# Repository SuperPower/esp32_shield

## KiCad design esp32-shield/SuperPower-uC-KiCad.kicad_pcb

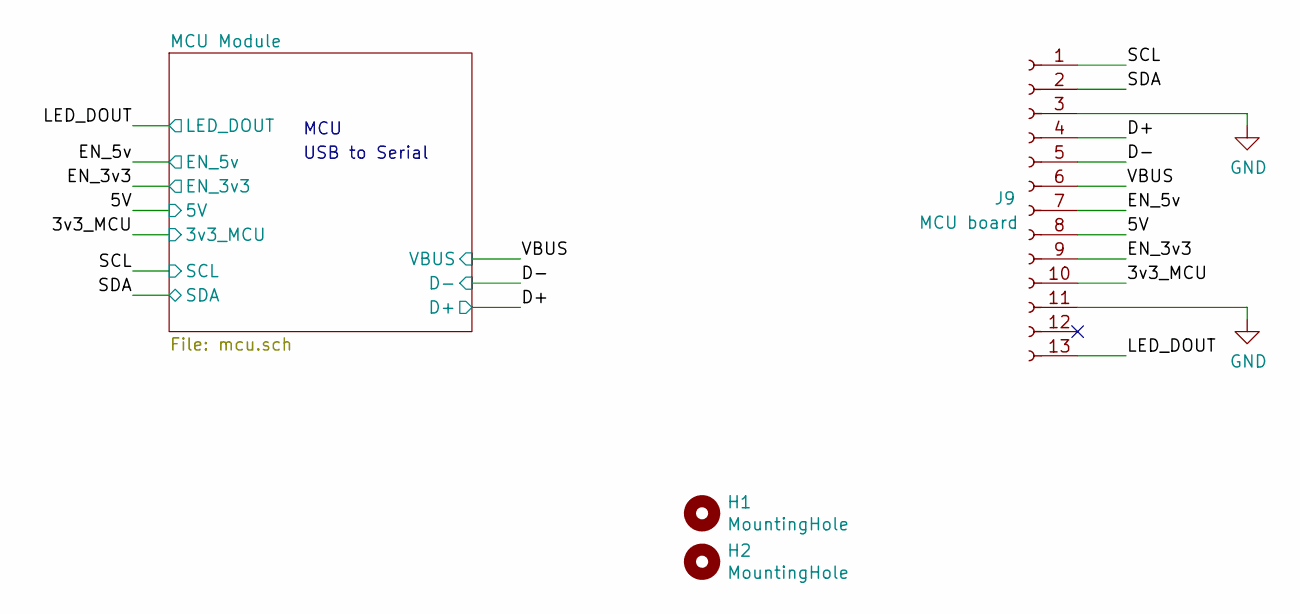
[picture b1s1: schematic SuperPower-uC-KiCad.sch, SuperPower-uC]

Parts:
H1, H2: MountingHole; MountingHole_2.7mm_M2.5_ISO7380
J9: MCU board; PinHeader_1x13_P2.54mm_Vertical

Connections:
/3v3_MCU: J9.10; also elsewhere on the board
/5V: J9.8; also elsewhere on the board
/D+: J9.4; also elsewhere on the board
/D-: J9.5; also elsewhere on the board
/EN_3v3: J9.9; also elsewhere on the board
/EN_5v: J9.7; also elsewhere on the board
/LED_DOUT: J9.13; also elsewhere on the board
/SCL: J9.1; also elsewhere on the board
/SDA: J9.2; also elsewhere on the board
/VBUS: J9.6; also elsewhere on the board
GND: J9.3, J9.11; also elsewhere on the board

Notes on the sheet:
MCU
USB to Serial

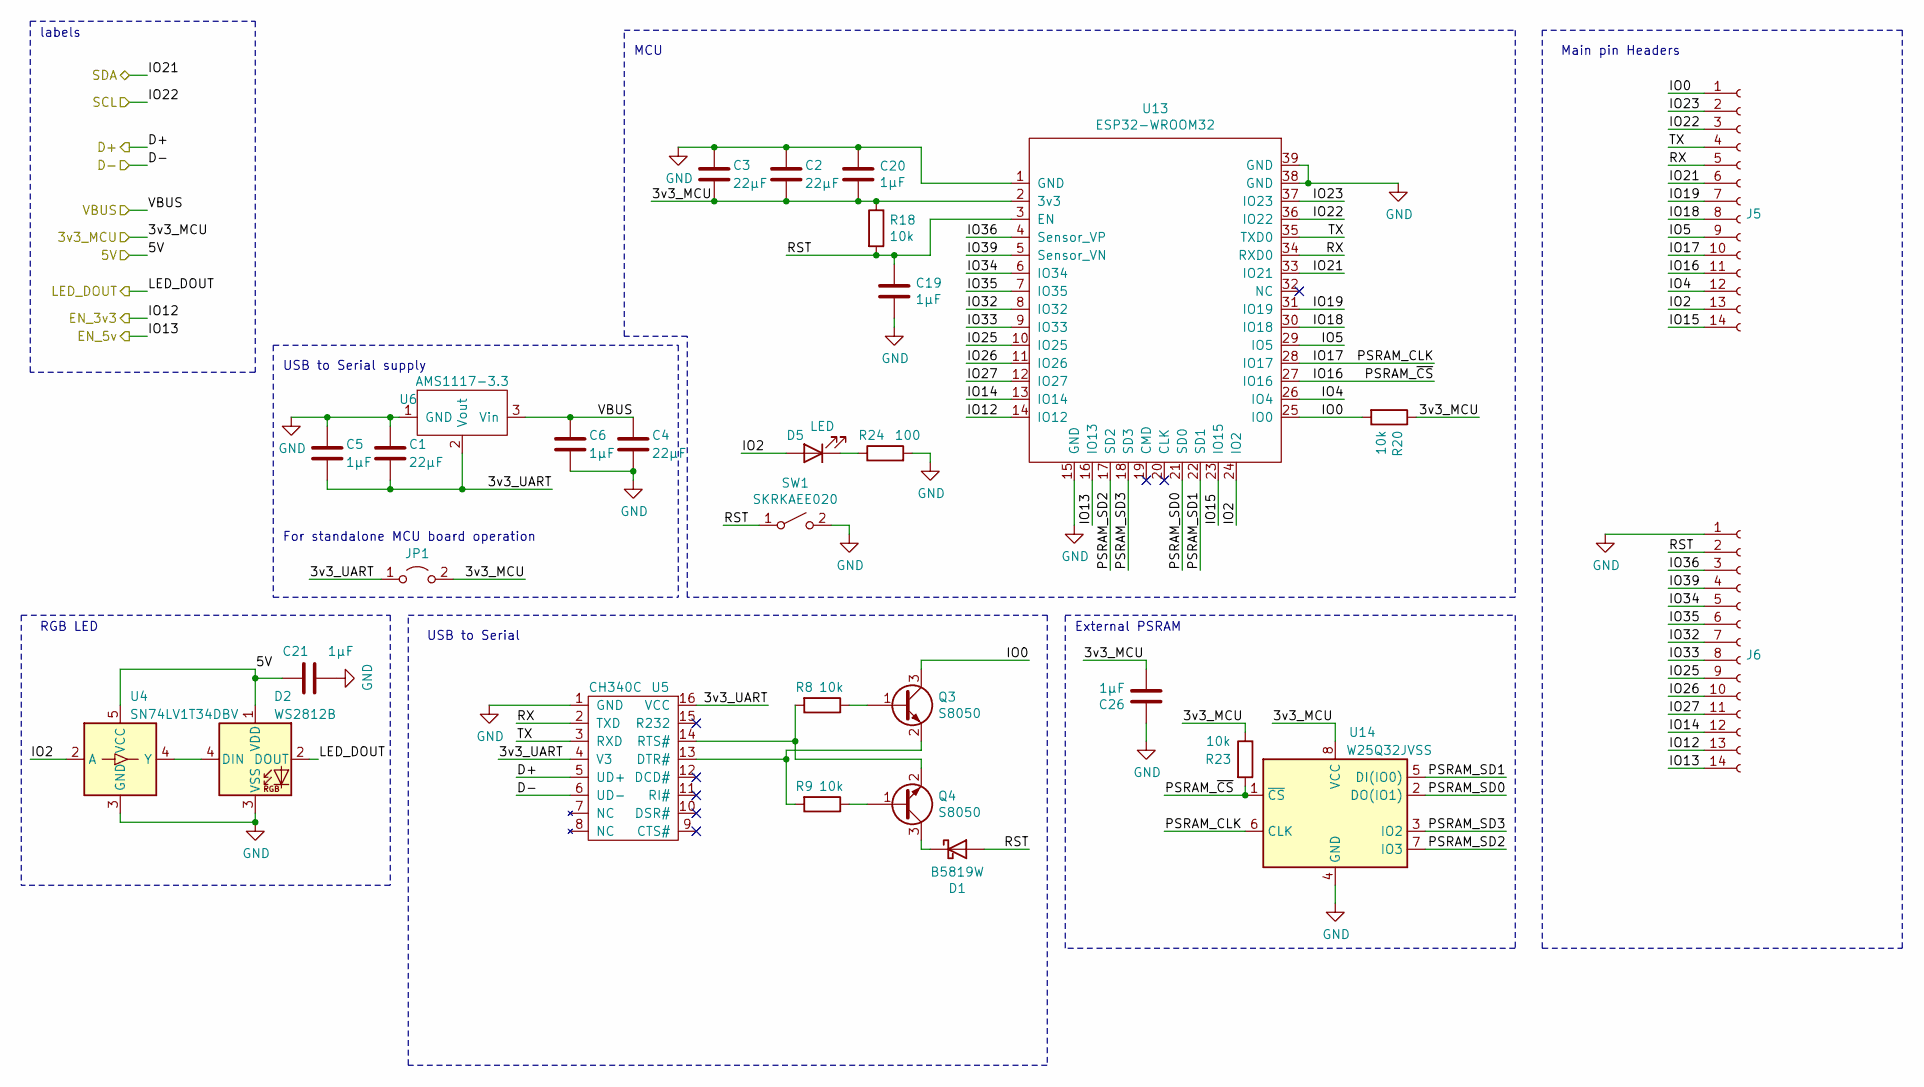
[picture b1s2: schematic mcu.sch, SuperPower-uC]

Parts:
C1, C2, C3, C4: 22µF; C_0805_2012Metric; LCSC C45783
C5, C6, C19, C20, C21, C26: 1µF; C_0603_1608Metric; LCSC C15849
D1: B5819W; D_SOD-123; LCSC C8598
D2: WS2812B; LED_WS2812B_PLCC4_5.0x5.0mm_P3.2mm; LCSC C114586
D5: LED; LED_0603_1608Metric_Pad1.05x0.95mm_HandSolder; LCSC C72041
J5, J6: Conn_01x14_Female; PinSocket_1x14_P2.54mm_Vertical
JP1: Jumper_2_Open; SolderJumper-2_P1.3mm_Open_Pad1.0x1.5mm
Q3, Q4: S8050; SOT-23_Handsoldering; LCSC C2146
R8, R9, R18, R20, R23: 10k; R_0603_1608Metric_Pad1.05x0.95mm_HandSolder; LCSC C25804
R24: 100; R_0603_1608Metric_Pad1.05x0.95mm_HandSolder; LCSC C22775
SW1: SKRKAEE020; SW_Push_SPST_NO_Alps_SKRK; LCSC C115357
U4: SN74LV1T34DBV; SOT-23-5; LCSC C100024
U5: CH340C; SOP-16_4.55x10.3mm_P1.27mm; LCSC C84681
U6: AMS1117-3.3; SOT-223-3_TabPin2; LCSC C6186
U13: ESP32-WROOM32; ESP32-WROOM-32; LCSC C82899
U14: W25Q32JVSS; SOIC-8_5.23x5.23mm_P1.27mm; LCSC C25804

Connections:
/3v3_MCU: C2.2, C3.2, C20.2, C26.2, JP1.2 (B), R18.1, R20.1, R23.1, U13.2 (3v3), U14.8 (VCC); also elsewhere on the board
/5V: C21.1, D2.1 (VDD), U4.5 (VCC); also elsewhere on the board
/D+: U5.5 (UD+); also elsewhere on the board
/D-: U5.6 (UD-); also elsewhere on the board
/EN_3v3: J6.13, U13.14 (IO12); also elsewhere on the board
/EN_5v: J6.14, U13.16 (IO13); also elsewhere on the board
/LED_DOUT: D2.2 (DOUT); also elsewhere on the board
/MCU Module/3v3_UART: C1.2, C5.2, JP1.1 (A), U5.4 (V3), U5.16 (VCC), U6.2 (Vout)
/MCU Module/IO0: J5.1, Q3.3 (C), R20.2, U13.25 (IO0)
/MCU Module/IO2: D5.2 (A), J5.13, U4.2 (A), U13.24 (IO2)
/MCU Module/IO4: J5.12, U13.26 (IO4)
/MCU Module/IO5: J5.9, U13.29 (IO5)
/MCU Module/IO14: J6.12, U13.13 (IO14)
/MCU Module/IO15: J5.14, U13.23 (IO15)
/MCU Module/IO16: J5.11, R23.2, U13.27 (IO16), U14.1 (~CS)
/MCU Module/IO17: J5.10, U13.28 (IO17), U14.6 (CLK)
/MCU Module/IO18: J5.8, U13.30 (IO18)
/MCU Module/IO19: J5.7, U13.31 (IO19)
/MCU Module/IO23: J5.2, U13.37 (IO23)
/MCU Module/IO25: J6.9, U13.10 (IO25)
/MCU Module/IO26: J6.10, U13.11 (IO26)
/MCU Module/IO27: J6.11, U13.12 (IO27)
/MCU Module/IO32: J6.7, U13.8 (IO32)
/MCU Module/IO33: J6.8, U13.9 (IO33)
/MCU Module/IO34: J6.5, U13.6 (IO34)
/MCU Module/IO35: J6.6, U13.7 (IO35)
/MCU Module/IO36: J6.3, U13.4 (Sensor_VP)
/MCU Module/IO39: J6.4, U13.5 (Sensor_VN)
/MCU Module/PSRAM_SD0: U13.21 (SD0), U14.2 (DO(IO1))
/MCU Module/PSRAM_SD1: U13.22 (SD1), U14.5 (DI(IO0))
/MCU Module/PSRAM_SD2: U13.17 (SD2), U14.7 (IO3)
/MCU Module/PSRAM_SD3: U13.18 (SD3), U14.3 (IO2)
/MCU Module/RST: C19.1, D1.2 (A), J6.2, R18.2, SW1.1 (A), U13.3 (EN)
/MCU Module/RX: J5.5, U5.2 (TXD), U13.34 (RXD0)
/MCU Module/TX: J5.4, U5.3 (RXD), U13.35 (TXD0)
/SCL: J5.3, U13.36 (IO22); also elsewhere on the board
/SDA: J5.6, U13.33 (IO21); also elsewhere on the board
/VBUS: C4.1, C6.1, U6.3 (Vin); also elsewhere on the board
GND: C1.1, C2.1, C3.1, C4.2, C5.1, C6.2, C19.2, C20.1, C21.2, C26.1, D2.3 (VSS), J6.1, R24.2, SW1.2 (B), U4.3 (GND), U5.1 (GND), U6.1 (GND), U13.1 (GND), U13.15 (GND), U13.38 (GND), U13.39 (GND), U14.4 (GND); also elsewhere on the board
unnamed: D1.1 (K), Q4.3 (C)
unnamed: D2.4 (DIN), U4.4 (Y)
unnamed: D5.1 (K), R24.1
unnamed: Q3.1 (B), R8.1
unnamed: Q3.2 (E), R9.2, U5.13 (DTR#)
unnamed: Q4.1 (B), R9.1
unnamed: Q4.2 (E), R8.2, U5.14 (RTS#)

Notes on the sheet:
MCU
labels
Main pin Headers
USB to Serial supply
USB to Serial
For standalone MCU board operation
External PSRAM
RGB LED

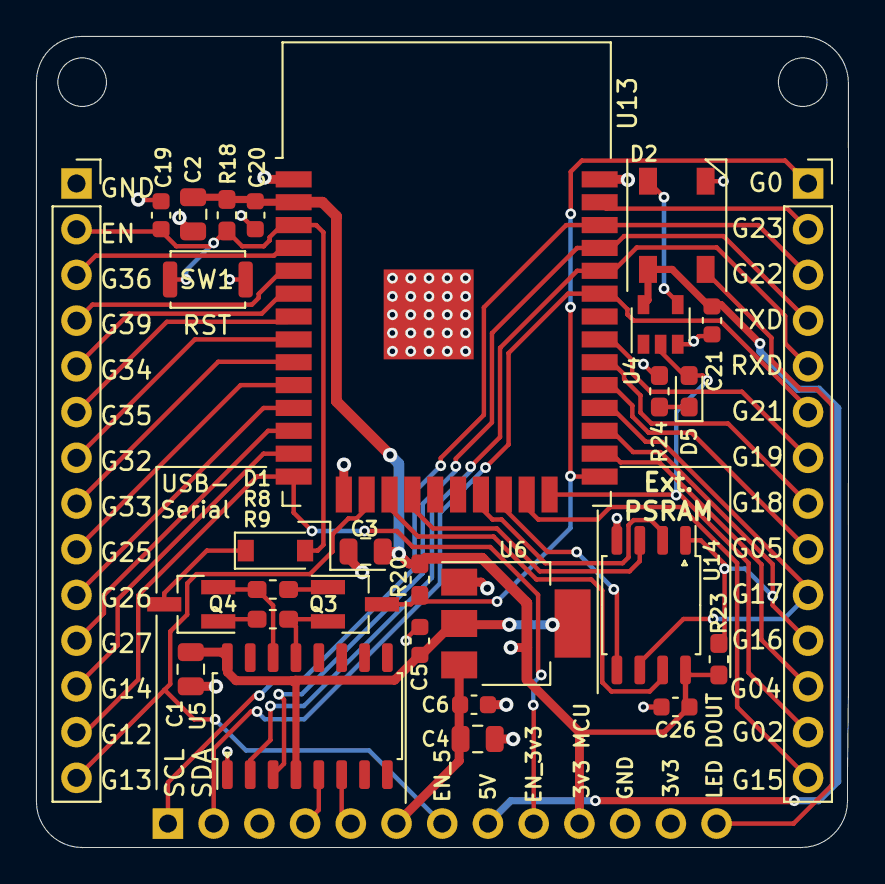
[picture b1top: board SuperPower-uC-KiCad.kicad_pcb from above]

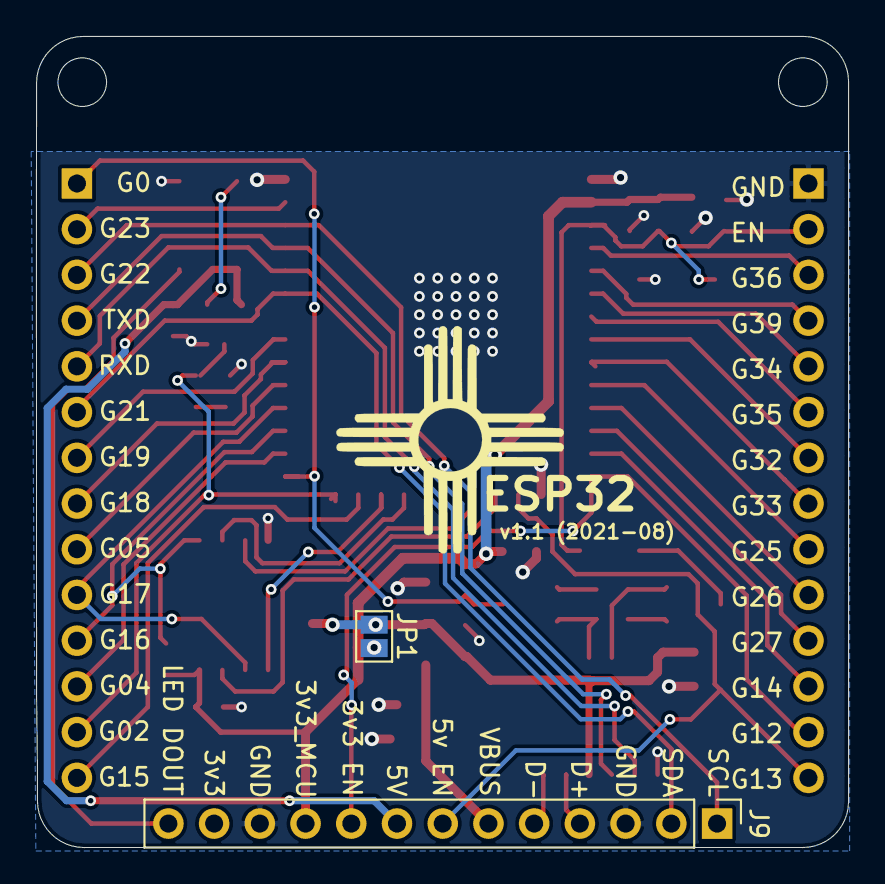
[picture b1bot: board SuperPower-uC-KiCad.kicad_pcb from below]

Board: 2 copper layers, 45.1 x 45.1 mm, 33 parts (2 on the bottom side), 46 nets.

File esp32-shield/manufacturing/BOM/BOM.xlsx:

Qty | References | Value | Footprint | DNP
5.0 | C5, C6, C19, C20, C21 | 1µF | C_0603_1608Metric
1.0 | C26 | DNP/1µF | C_0603_1608Metric | DNP
4.0 | C1, C2, C3, C4 | 22µF | C_0805_2012Metric
4.0 | R8, R9, R18, R20 | 10k | R_0603_1608Metric_Pad1.05x0.95mm_HandSolder
1.0 | R23 | DNP/10k | R_0603_1608Metric_Pad1.05x0.95mm_HandSolder | DNP
1.0 | R24 | 100R | R_0603_1608Metric_Pad1.05x0.95mm_HandSolder
1.0 | D1 | B5819W | D_SOD-123
1.0 | D5 | LED | LED_0603_1608Metric_Pad1.05x0.95mm_HandSolder
1.0 | D2 | WS2812B | LED_WS2812B_PLCC4_5.0x5.0mm_P3.2mm
1.0 | U13 | ESP32-WROOM32 | ESP32-WROOM-32
1.0 | U14 | DNP/W25Q32JVSS | SOIC-8_5.23x5.23mm_P1.27mm | DNP
1.0 | U5 | CH340C | SOP-16_4.55x10.3mm_P1.27mm
1.0 | U6 | AMS1117-3.3 | SOT-223-3_TabPin2
1.0 | U4 | SN74LV1T34DBV | SOT-23-5
1.0 | SW1 | SKRKAEE020 | SW_Push_SPST_NO_Alps_SKRK
2.0 | Q3, Q4 | S8050 | SOT-23_Handsoldering
1.0 | J9 | MCU board | PinHeader_1x13_P2.54mm_Vertical
2.0 | J5, J6 | DNP/Conn_01x14_Female | PinSocket_1x14_P2.54mm_Vertical | DNP

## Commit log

2021-02-17 changed naming of usb to serial stuff and added led to mcu board
2021-02-17 disconnected 5v_EN and 3v3_EN from the pin header on the regulator board
2021-02-21 Moved repo and made it esp32-shield only files
2021-02-22 deleted unused files and renamed net lables
2021-02-23 added rgbw led, swapped ch340g for ch340c part numers
    also marked crystal and caps as DNP
2021-03-05 added more input caps & part number for button
2021-03-08 fixed drc
2021-03-08 changed switch value
2021-04-02 removed led pin 1 marking and added corner on silk
2021-05-24 swapped button lcsc part number for cheaper alps one
2021-05-27 swapped led for WS2812 footprint with logic level shifter
2021-05-27 added more silk labels where there was space
2021-05-28 updated pcb version number and date
2021-05-29 RGB led on right side and using pin 2
2021-05-29 rearranged tracks on left side
2021-05-30 some minor silk and routing improvements
2021-06-07 added another 22µ cap to 3v3mcu rail
2021-06-22 swapped .1µ caps for 1µ caps
2021-07-06 changed CH340G to CH340C, deleted crystal footprint and caps, added caps
2021-07-09 swapped jumper with solderbridge
2021-08-02 fixed silk positioning
2021-08-04 Marked components DNP
2021-08-04 Created BOM + removed old files
2021-08-04 Generated Gerber files
2022-02-03 organized production files and added lcsc part numbers
2022-04-28 added part numbers and extended ref
2022-05-07 updated production files

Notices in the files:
SuperPower-uC/lowcostStack/SuperPower-uC-KiCad.sch:
Licence: CERN-OHL-W
